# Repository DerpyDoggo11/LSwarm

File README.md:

# LSwarm Mk.1
Micro-drone swarm as a light display

## 3D Preview

## Wiring

## Schematic

### Download ./latestProduction to begin fabricating the PCB

## Introduction
The LSwarm Mk.1 is a cheap open-source microdrone platform for making drone swarms. Instead of GPS, it uses UWB frequencies to communicate with ground anchors (see [LS Anchor](https://github.com/DerpyDoggo11/LSwarm-Anchor)) for positioning. To fabricate these drones yourself, see the bill of materials below and follow the instructions. 

Also, its all open sourced under the GNU GPL license! (do what you will with the code and designs but make sure to keep it open-source! :D)

### Are drone swarms legal in the US?
TLDR: yes and no, mostly no but sometimes yes. 

In the US, flying more than one drone by yourself outside is technically not legal without a permit, but flying indoors (or under some netting outside) is perfectly allowed, so make sure you understand this before buying or assembling any components.

If you live outside of the US, your restrictions will be different so make sure to check with your local government. 

## Bill of Materials 

### (Minimum build for testing: 5 drones)

| Quantity | Components | Price | Link |
|--------- |----------|----------| -----|
| 20  | Brushed DC Motors | ~$9.68 | [here](https://www.aliexpress.us/item/3256810271706869.html?spm=a2g0o.productlist.main.48.18214690sK1aRt&algo_pvid=53df9bc5-14d9-4ef0-b69f-11a93d529ec5&algo_exp_id=53df9bc5-14d9-4ef0-b69f-11a93d529ec5-45&)
| 5  | 1s 450mAh BT2.0 Batteries | ~$11.21 | [here](https://www.aliexpress.us/item/3256810349502140.html?spm=a2g0o.productlist.main.9.7055TeWnTeWnyW&algo_pvid=e87d392e-a216-4ba3-8956-baf637a8cba3&algo_exp_id=e87d392e-a216-4ba3-8956-baf637a8cba3-8&pdp_ext_f=%7B%22order%22%3A%2248%22%2C%22eval%22%3A%221%22%2C%22fromPage%22%3A%22search%22%7D&pdp_npi=6%40dis%21USD%2113.57%216.78%21%21%2192.34%2146.17%21%402103110517771681621716757e4b37%2112000052738741335%21sea%21US%217493938711%21X%211%210%21n_tag%3A-29913%3Bd%3Ad260408f%3Bm03_new_user%3A-29895&curPageLogUid=6cUgOJiOwfNW&utparam-url=scene%3Asearch%7Cquery_from%3A%7Cx_object_id%3A1005010535816892%7C_p_origin_prod%3A)
| 1 | 1s BT2.0 Charger | ~18.18 | [here](https://www.aliexpress.us/item/3256811772590472.html?spm=a2g0o.productlist.main.3.315a3kxV3kxVU5&algo_pvid=a57de163-f3db-4a1d-966e-e88601147021&algo_exp_id=a57de163-f3db-4a1d-966e-e88601147021-2&pdp_ext_f=%7B%22order%22%3A%22-1%22%2C%22eval%22%3A%221%22%2C%22fromPage%22%3A%22search%22%7D&pdp_npi=6%40dis%21USD%2131.82%2119.09%21%21%21216.43%21129.86%21%402101f54117771690026201319e9264%2112000057143664294%21sea%21US%217493938711%21X%211%210%21n_tag%3A-29913%3Bd%3Ad260408f%3Bm03_new_user%3A-29895&curPageLogUid=pie8lE5eVKgd&utparam-url=scene%3Asearch%7Cquery_from%3A%7Cx_object_id%3A1005011958905224%7C_p_origin_prod%3A) 
|5 | 2.4G Wifi Antenna | ~$3.52 | [here](https://www.aliexpress.us/item/3256802833801038.html?spm=a2g0o.productlist.main.17.44bbCrBdCrBdFl&algo_pvid=20d56933-2b0c-45d5-8601-1bc6a9682401&algo_exp_id=20d56933-2b0c-45d5-8601-1bc6a9682401-16&pdp_ext_f=%7B%22order%22%3A%221074%22%2C%22eval%22%3A%221%22%2C%22fromPage%22%3A%22search%22%7D&pdp_npi=6%40dis%21USD%213.55%213.52%21%21%213.55%213.52%21%402101ef5e17781321493642302e40a6%2112000023272348781%21sea%21US%217493938711%21X%211%210%21n_tag%3A-29913%3Bd%3A21b1ce8d%3Bm03_new_user%3A-29895&curPageLogUid=rLnZuf4b98Bi&utparam-url=scene%3Asearch%7Cquery_from%3A%7Cx_object_id%3A1005003020115790%7C_p_origin_prod%3A)
| 5 | BMP581 (hand solder) | ~$20.34 | [here](https://www.lcsc.com/product-detail/C5362283.html?s_z=s_p_BMP581&spm=wm.ssy.bg.0.xh&lcsc_vid=EQdcXlMFQFgMVQUCQlALX1cFQVFeBlwHRgVYV1UAEwUxVlNRT1BfUFdfTlJcUDsOAxUeFF5JWBYZEEoKFBINSQcJGk4dAgUUFAk%3D)
| 5 | LSM6DSRTR (hand solder) | ~$17.33 | [here](https://www.lcsc.com/product-detail/C784817.html?s_z=s_q_LSM6DSR&spm=wm.ssy.bg.0.xh&lcsc_vid=EQdcXlMFQFgMVQUCQlALX1cFQVFeBlwHRgVYV1UAEwUxVlNRT1BfUFdTRFdfVDsOAxUeFF5JWBYZEEoKFBINSQcJGk4dAgUUFAk%3D)
| 5  | Mk.1 PCBs | ~$125 (with shipping, cost can vary widely however) | Download repo, extract fabrication files, and fabricate through JLCPCB (complete instructions for this may come soon)

Total cost: **$218.49**

Cost per drone: **$41.76**

----

### (Ideal build for full display: 20 drones)

| Quantity | Components | Price | Link |
|--------- |----------|----------| -----|
| 80  | Brushed DC Motors | ~$54.88  | [here](https://www.aliexpress.us/item/3256810271706869.html?spm=a2g0o.productlist.main.48.18214690sK1aRt&algo_pvid=53df9bc5-14d9-4ef0-b69f-11a93d529ec5&algo_exp_id=53df9bc5-14d9-4ef0-b69f-11a93d529ec5-45&)
| 20  | 1s 450mAh BT2.0 Batteries | ~$61.82  | [here](https://www.aliexpress.us/item/3256810349502140.html?spm=a2g0o.productlist.main.9.7055TeWnTeWnyW&algo_pvid=e87d392e-a216-4ba3-8956-baf637a8cba3&algo_exp_id=e87d392e-a216-4ba3-8956-baf637a8cba3-8&pdp_ext_f=%7B%22order%22%3A%2248%22%2C%22eval%22%3A%221%22%2C%22fromPage%22%3A%22search%22%7D&pdp_npi=6%40dis%21USD%2113.57%216.78%21%21%2192.34%2146.17%21%402103110517771681621716757e4b37%2112000052738741335%21sea%21US%217493938711%21X%211%210%21n_tag%3A-29913%3Bd%3Ad260408f%3Bm03_new_user%3A-29895&curPageLogUid=6cUgOJiOwfNW&utparam-url=scene%3Asearch%7Cquery_from%3A%7Cx_object_id%3A1005010535816892%7C_p_origin_prod%3A)
| 2 | 1s BT2.0 Charger | ~$36.36 | [here](https://www.aliexpress.us/item/3256811772590472.html?spm=a2g0o.productlist.main.3.315a3kxV3kxVU5&algo_pvid=a57de163-f3db-4a1d-966e-e88601147021&algo_exp_id=a57de163-f3db-4a1d-966e-e88601147021-2&pdp_ext_f=%7B%22order%22%3A%22-1%22%2C%22eval%22%3A%221%22%2C%22fromPage%22%3A%22search%22%7D&pdp_npi=6%40dis%21USD%2131.82%2119.09%21%21%21216.43%21129.86%21%402101f54117771690026201319e9264%2112000057143664294%21sea%21US%217493938711%21X%211%210%21n_tag%3A-29913%3Bd%3Ad260408f%3Bm03_new_user%3A-29895&curPageLogUid=pie8lE5eVKgd&utparam-url=scene%3Asearch%7Cquery_from%3A%7Cx_object_id%3A1005011958905224%7C_p_origin_prod%3A) 
| 20 | 2.4G Wifi Antenna | ~$14.08 | [here](https://www.aliexpress.us/item/3256802833801038.html?spm=a2g0o.productlist.main.17.44bbCrBdCrBdFl&algo_pvid=20d56933-2b0c-45d5-8601-1bc6a9682401&algo_exp_id=20d56933-2b0c-45d5-8601-1bc6a9682401-16&pdp_ext_f=%7B%22order%22%3A%221074%22%2C%22eval%22%3A%221%22%2C%22fromPage%22%3A%22search%22%7D&pdp_npi=6%40dis%21USD%213.55%213.52%21%21%213.55%213.52%21%402101ef5e17781321493642302e40a6%2112000023272348781%21sea%21US%217493938711%21X%211%210%21n_tag%3A-29913%3Bd%3A21b1ce8d%3Bm03_new_user%3A-29895&curPageLogUid=rLnZuf4b98Bi&utparam-url=scene%3Asearch%7Cquery_from%3A%7Cx_object_id%3A1005003020115790%7C_p_origin_prod%3A)
| 20 | BMP581 (hand solder) | ~$74.76 | [here](https://www.lcsc.com/product-detail/C5362283.html?s_z=s_p_BMP581&spm=wm.ssy.bg.0.xh&lcsc_vid=EQdcXlMFQFgMVQUCQlALX1cFQVFeBlwHRgVYV1UAEwUxVlNRT1BfUFdfTlJcUDsOAxUeFF5JWBYZEEoKFBINSQcJGk4dAgUUFAk%3D)
| 20 | LSM6DSRTR (hand solder) | ~$60.13 | [here](https://www.lcsc.com/product-detail/C784817.html?s_z=s_q_LSM6DSR&spm=wm.ssy.bg.0.xh&lcsc_vid=EQdcXlMFQFgMVQUCQlALX1cFQVFeBlwHRgVYV1UAEwUxVlNRT1BfUFdTRFdfVDsOAxUeFF5JWBYZEEoKFBINSQcJGk4dAgUUFAk%3D)
| 20  | Mk.1 PCBs | ~$200 (with shipping, cost can vary widely however) | Download repo, extract fabrication files, and fabricate through JLCPCB (complete instructions for this may come soon)

Total cost: **$562.95**

Cost per drone: **$25.40**

----

## Tools / Other parts:
- Raspberry PI Zero 2 W or equivalent (or just a computer/laptop)
- UWB Anchors ([LS Anchor](https://github.com/DerpyDoggo11/LSwarm-Anchor) or equivalent UWB module (must have wifi)) 
- Hot-air reflow station or SMD hot plate
- Solder paste for SMD components
- Tweezers for SMD components
- Soldering iron + solder
- Wire strippers/cutters
- Zipties, tape, or velcro straps
- Hot glue + hot glue gun

## Assembly
1. Apply solder paste onto the smd joints for the BMP581 and LSM6DSRTR.
2. Carefully align the components and place using tweezers
3. Use a hot-air gun (preferred over smd hot plate to not mess up any other components) on high heat to quickly heat up the solder paste (prolonged heat may damage components)
4. Fit motors into mounting holes (make sure they are aligned properly on all sides) use wire strippers to cut and solder on motor wires. Apply hot glue or equivalent to the motors to keep them in place.
5. Use wire strippers to cut and solder on battery connector wires to PCB.
6. Attach battery with velcro, zipties, or tape.
7. Plug in battery and flash software with the USB-C port.

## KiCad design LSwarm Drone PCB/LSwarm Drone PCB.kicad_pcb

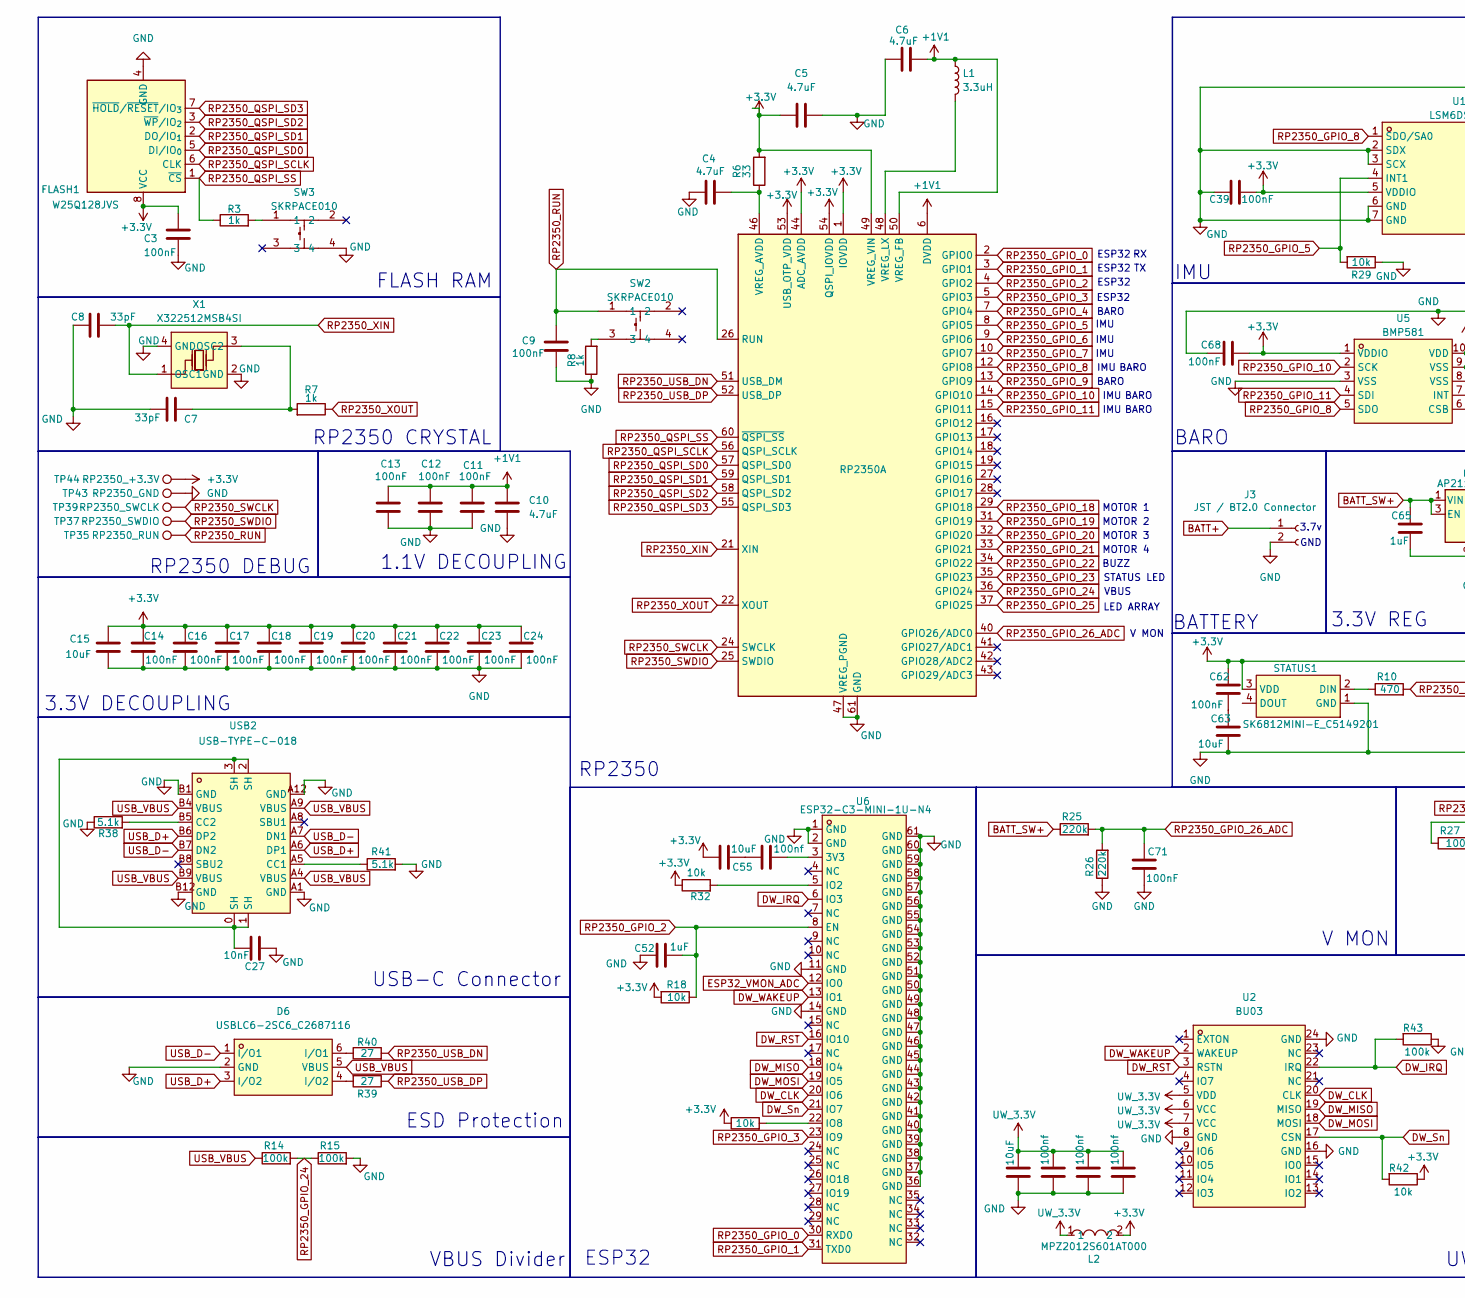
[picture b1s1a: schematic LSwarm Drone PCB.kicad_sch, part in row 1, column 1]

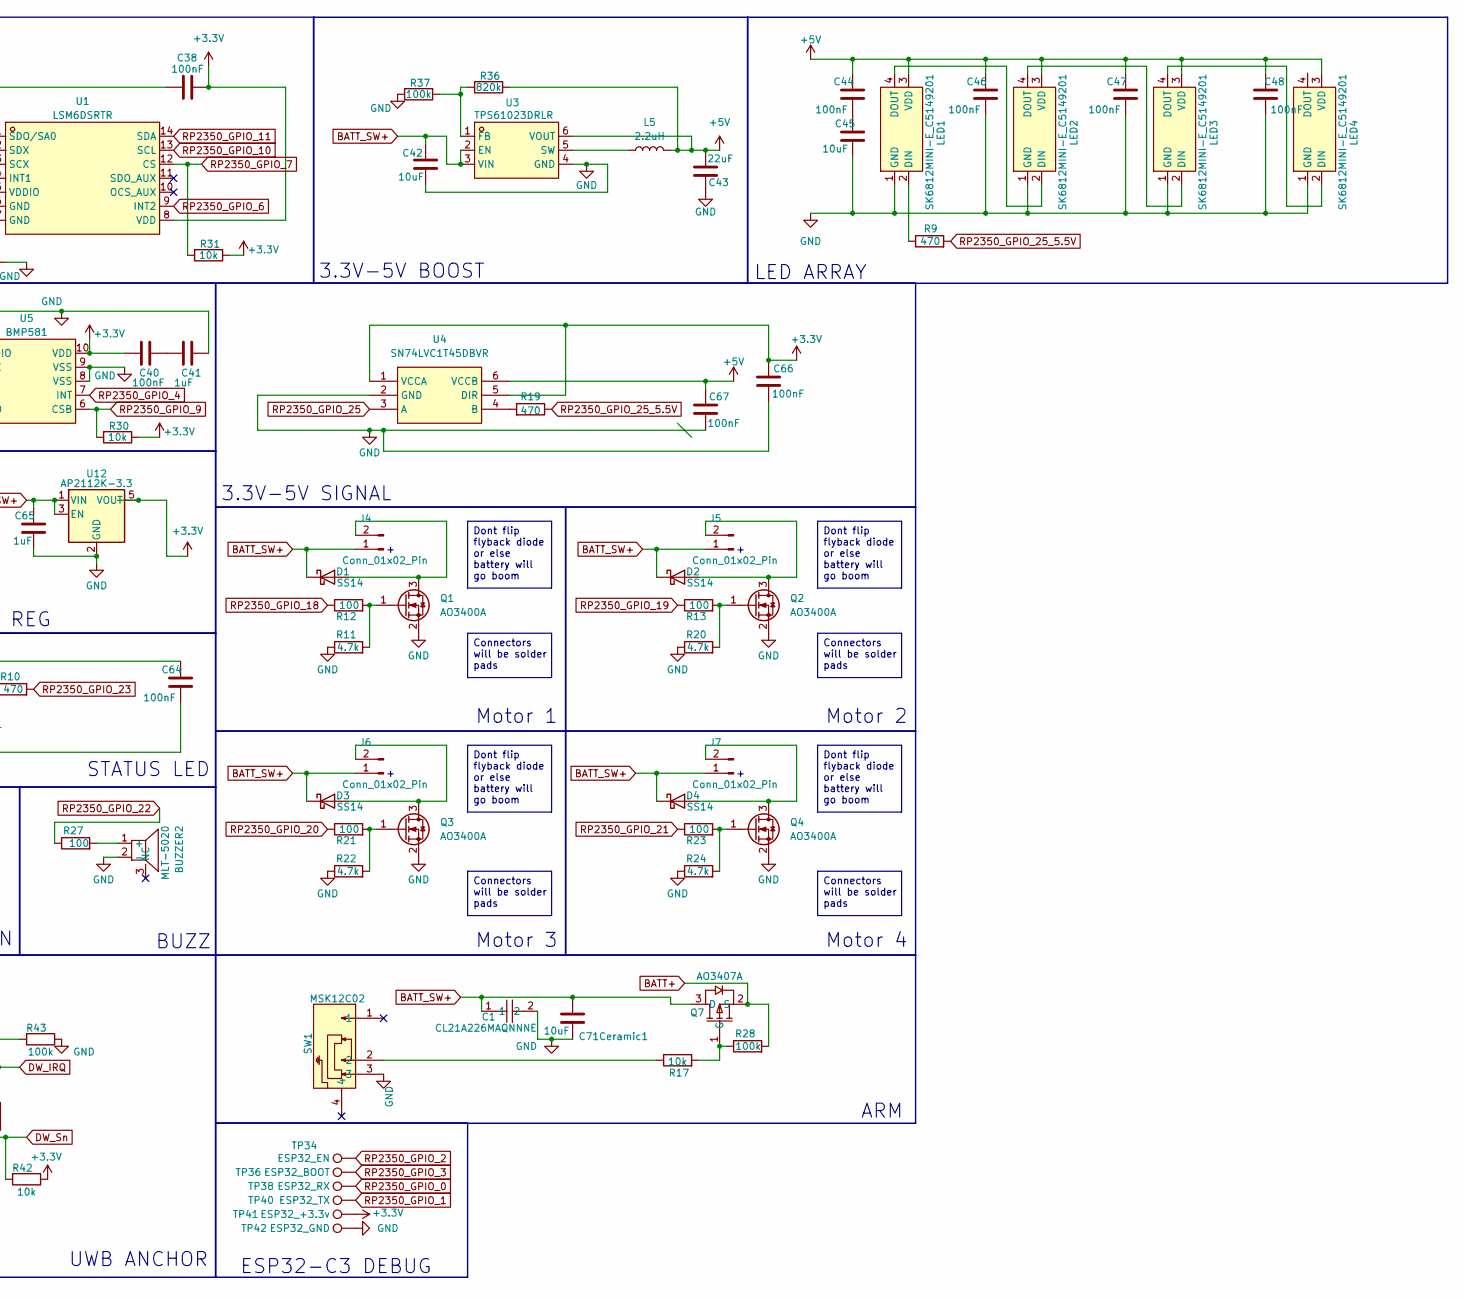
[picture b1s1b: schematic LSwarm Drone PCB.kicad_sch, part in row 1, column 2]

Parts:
BUZZER2: MLT-5020; BUZ-SMD_L5.0-W5.5-P4.60; MPN MLT-5020; LCSC Part C94598
C1: CL21A226MAQNNNE; C0805; MPN CL21A226MAQNNNE; LCSC Part C45783
C3, C9, C11, C12, C13, C14, C16, C17, C18, C19, C20, C21, C22, C23, C24, C38, C39, C40, C44, C46, C47, C48, C62, C64, C66, C67, C68, C71: 100nF; C_0603_1608Metric
C4, C5, C6, C10: 4.7uF; C_0603_1608Metric
C7, C8: 33pF; C_0603_1608Metric
C15, C42, C45, C63, C71Ceramic1: 10uF; C_0805_2012Metric
C27: 10nF; C_0603_1608Metric
C41, C52, C65: 1uF; C_0603_1608Metric
C43: 22uF; C_0805_2012Metric
C55, C69: 10uF; C_0603_1608Metric
C56, C58, C59, C61: 100nf; C_0603_1608Metric
D1, D2, D3, D4: SS14; D_SMA
D6: USBLC6-2SC6_C2687116; SOT-23-6_L2.9-W1.6-P0.95-LS2.8-BL; MPN USBLC6-2SC6; LCSC Part C2687116
FLASH1: W25Q128JVS; SOIC-8_5.3x5.3mm_P1.27mm
J3: JST / BT2.0 Connector; JST_PH_S2B-PH-K_1x02_P2.00mm_Horizontal
J4, J5, J6, J7: Conn_01x02_Pin; PinHeader_1x02_P2.54mm_Vertical
L1: 3.3uH; L_1210_3225Metric
L2: MPZ2012S601AT000; L0805; MPN MPZ2012S601AT000; LCSC Part C21519
L5: 2.2uH; L_1210_3225Metric
LED1, LED2, LED3, LED4: SK6812MINI-E_C5149201; LED-SMD_4P-L3.2-W2.8-LS5.9_SK6812MINI-E; MPN SK6812MINI-E; LCSC Part C5149201
Q1, Q2, Q3, Q4: AO3400A; SOT-23
Q7: AO3407A; SOT-23-3_L2.9-W1.6-P1.90-LS2.8-BR; MPN AO3407A; LCSC Part C15155
R3, R7, R8: 1k; R_0603_1608Metric
R6: 33; R_0603_1608Metric
R9, R10, R19: 470; R_0603_1608Metric
R11, R20, R22, R24: 4.7k; R_0603_1608Metric
R12, R13, R21, R23, R27: 100; R_0603_1608Metric
R14, R15, R28, R37, R43: 100k; R_0603_1608Metric
R17, R18, R29, R30, R31, R32, R33, R42: 10k; R_0603_1608Metric
R25, R26: 220k; R_0603_1608Metric
R36: 820k; R_0603_1608Metric
R38, R41: 5.1k; R_0603_1608Metric
R39, R40: 27; R_0603_1608Metric
RP2350: RP2350A; QFN-60-1EP_7x7mm_P0.4mm_EP3.4x3.4mm
STATUS1: SK6812MINI-E_C5149201; LED-SMD_4P-L3.2-W2.8-LS5.9_SK6812MINI-E; MPN SK6812MINI-E; LCSC Part C5149201
SW1: MSK12C02; SW-TH_MSK12C02; MPN MSK12C02; LCSC Part C431540
SW2, SW3: SKRPACE010; KEY-SMD_4P-L4.2-W3.2-P2.20-LS4.6; MPN SKRPACE010; LCSC Part C139797
TP34: ESP32_EN; TestPoint_Pad_1.0x1.0mm
TP35: RP2350_RUN; TestPoint_Pad_1.0x1.0mm
TP36: ESP32_BOOT; TestPoint_Pad_1.0x1.0mm
TP37: RP2350_SWDIO; TestPoint_Pad_1.0x1.0mm
TP38: ESP32_RX; TestPoint_Pad_1.0x1.0mm
TP39: RP2350_SWCLK; TestPoint_Pad_1.0x1.0mm
TP40: ESP32_TX; TestPoint_Pad_1.0x1.0mm
TP41: ESP32_+3.3v; TestPoint_Pad_1.0x1.0mm
TP42: ESP32_GND; TestPoint_Pad_1.0x1.0mm
TP43: RP2350_GND; TestPoint_Pad_1.0x1.0mm
TP44: RP2350_+3.3V; TestPoint_Pad_1.0x1.0mm
U1: LSM6DSRTR; LGA-14_L3.0-W2.5-P0.50-BR; MPN LSM6DSRTR; LCSC Part C784817
U2: BU03; WIRELM-SMD_BU03; MPN BU03; LCSC Part C42419011
U3: TPS61023DRLR; SOT-563_L1.6-W1.2-P0.50-LS1.6-BR; MPN TPS61023DRLR; LCSC Part C919459
U4: SN74LVC1T45DBVR; SOT-23-6_L2.9-W1.6-P0.95-LS2.8-BR; MPN SN74LVC1T45DBVR; LCSC Part C7843
U5: BMP581; LGA-10_L2.0-W2.0-P0.50-TL_BMP581; MPN BMP581; LCSC Part C5362283
U6: ESP32-C3-MINI-1U-N4; WIFIM-SMD_61P-L13.2-W12.5-P0.80; MPN ESP32-C3-MINI-1U-N4; LCSC Part C2911374
U12: AP2112K-3.3; SOT-23-5
USB2: USB-TYPE-C-018; USB-C_SMD-TYPE-C-31-M-12; MPN USB-TYPE-C-018; LCSC Part C2927038
X1: X322512MSB4SI; CRYSTAL-SMD_4P-L3.2-W2.5-BL; MPN X322512MSB4SI; LCSC Part C9002

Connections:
+1V1: C6.2, C10.1, C11.1, C12.1, C13.1, L1.1, RP2350.6 (DVDD), RP2350.23 (DVDD), RP2350.39 (DVDD), RP2350.50 (VREG_FB)
+3.3V: C3.1, C5.1, C14.1, C15.1, C16.1, C17.1, C18.1, C19.1, C20.1, C21.1, C22.1, C23.1, C24.1, C38.1, C39.1, C40.2, C55.2, C62.2, C64.2, C66.2, C68.1, FLASH1.8 (VCC), L2.2, R6.2, R18.2, R30.1, R31.1, R32.1, R33.1, R42.1, RP2350.1 (IOVDD), RP2350.11 (IOVDD), RP2350.20 (IOVDD), RP2350.30 (IOVDD), RP2350.38 (IOVDD), RP2350.44 (ADC_AVDD), RP2350.45 (IOVDD), RP2350.49 (VREG_VIN), RP2350.53 (USB_OTP_VDD), RP2350.54 (QSPI_IOVDD), STATUS1.3 (VDD), TP41.1 (1_1), TP44.1 (1_1), U1.5 (VDDIO), U1.8 (VDD), U4.1 (VCCA), U4.5 (DIR), U5.1 (VDDIO), U5.10 (VDD), U12.5 (VOUT)
+5V: C43.2, C44.2, C46.2, C47.2, C48.2, C67.2, L5.2, LED1.3 (VDD), LED2.3 (VDD), LED3.3 (VDD), LED4.3 (VDD), R36.1, U3.6 (VOUT), U4.6 (VCCB)
BATT+: J3.1, Q7.2 (S), R28.2
BATT_SW+: C1.1, C42.1, C65.2, C71Ceramic1.2, D1.1 (K), D2.1 (K), D3.1 (K), D4.1 (K), J4.1, J5.1, J6.1, J7.1, Q7.3 (D), R25.1, U3.2 (EN), U3.3 (VIN), U12.1 (VIN), U12.3 (EN)
DW_CLK: U2.20 (CLK), U6.20 (IO6)
DW_IRQ: R43.2, U2.22 (IRQ), U6.6 (IO3)
DW_MISO: U2.19 (MISO), U6.18 (IO4)
DW_MOSI: U2.18 (MOSI), U6.19 (IO5)
DW_RST: U2.3 (RSTN), U6.16 (IO10)
DW_Sn: R42.2, U2.17 (CSN), U6.21 (IO7)
DW_WAKEUP: U2.2 (WAKEUP), U6.13 (IO1)
ESP32_VMON_ADC: U6.12 (IO0)
GND: BUZZER2.2 (-), C1.2, C3.2, C4.1, C5.2, C6.1, C7.1, C8.2, C9.2, C10.2, C11.2, C12.2, C13.2, C14.2, C15.2, C16.2, C17.2, C18.2, C19.2, C20.2, C21.2, C22.2, C23.2, C24.2, C27.1, C38.2, C39.2, C41.1, C42.2, C43.1, C45.1, C46.1, C47.1, C48.1, C52.1, C58.2, C59.2, C61.2, C63.1, C64.1, C65.1, C66.1, C67.1, C68.2, C69.2, C71.1, C71Ceramic1.1, D6.2 (GND), FLASH1.4 (GND), J3.2, LED1.1 (GND), LED2.1 (GND), LED3.1 (GND), LED4.1 (GND), Q1.2 (S), Q2.2 (S), Q3.2 (S), Q4.2 (S), R8.1, R11.1, R15.2, R20.1, R22.1, R24.1, R26.1, R29.1, R37.2, R38.1, R41.2, R43.1, RP2350.47 (VREG_PGND), RP2350.61 (GND), STATUS1.1 (GND), SW1.3, SW3.4, TP42.1 (1_1), TP43.1 (1_1), U1.2 (SDX), U1.3 (SCX), U1.6 (GND), U1.7 (GND), U2.8 (GND), U2.16 (GND), U2.24 (GND), U3.4 (GND), U4.2 (GND), U5.3 (VSS), U5.8 (VSS), U5.9 (VSS), U6.1 (GND), U6.2 (GND), U6.11 (GND), U6.14 (GND), U6.36 (GND), U6.37 (GND), U6.38 (GND), U6.39 (GND), U6.40 (GND), U6.41 (GND), U6.42 (GND), U6.43 (GND), U6.44 (GND), U6.45 (GND), U6.46 (GND), U6.47 (GND), U6.48 (GND), U6.49 (GND), U6.50 (GND), U6.51 (GND), U6.52 (GND), U6.53 (GND), U6.54 (GND), U6.55 (GND), U6.56 (GND), U6.57 (GND), U6.58 (GND), U6.59 (GND), U6.60 (GND), U6.61 (GND), U12.2 (GND), USB2.A1 (GND), USB2.A12 (GND), USB2.B1 (GND), USB2.B12 (GND), X1.2 (GND), X1.4 (GND)
unnamed: BUZZER2.1 (+), R27.2
unnamed: C27.2, USB2.0 (SH), USB2.1 (SH), USB2.2 (SH), USB2.3 (SH)
unnamed: C40.1, C41.2
unnamed: C44.1, C45.2
unnamed: C55.1, C56.2
unnamed: C62.1, C63.2
unnamed: D1.2 (A), J4.2, Q1.3 (D)
unnamed: D2.2 (A), J5.2, Q2.3 (D)
unnamed: D3.2 (A), J6.2, Q3.3 (D)
unnamed: D4.2 (A), J7.2, Q4.3 (D)
unnamed: D6.6 (I/O1), R40.1
unnamed: D6.4 (I/O2), R39.2
unnamed: LED1.2 (DIN), R9.1
unnamed: LED1.4 (DOUT), LED2.2 (DIN)
unnamed: LED2.4 (DOUT), LED3.2 (DIN)
unnamed: LED3.4 (DOUT), LED4.2 (DIN)
unnamed: Q1.1 (G), R11.2, R12.2
unnamed: Q2.1 (G), R13.2, R20.2
unnamed: Q3.1 (G), R21.2, R22.2
unnamed: Q4.1 (G), R23.2, R24.2
unnamed: Q7.1 (G), R17.2, R28.1
unnamed: R3.2, SW3.1
unnamed: R8.2, SW2.3
unnamed: R17.1, SW1.2
unnamed: C4.2, R6.1, RP2350.46 (VREG_AVDD)
unnamed: L1.2, RP2350.48 (VREG_LX)
unnamed: R10.1, STATUS1.2 (DIN)
unnamed: R36.2, R37.1, U3.1 (FB)
unnamed: L5.1, U3.5 (SW)
unnamed: R19.2, U4.4 (B)
unnamed: C56.1, U6.3 (3V3)
unnamed: R32.2, U6.5 (IO2)
unnamed: R33.2, U6.22 (IO8)
unnamed: R41.1, USB2.A5 (CC1)
unnamed: R38.2, USB2.B5 (CC2)
unnamed: C7.2, R7.2, X1.3 (OSC2)
RP2350_GPIO_0: RP2350.2 (GPIO0), TP38.1 (1_1), U6.30 (RXD0)
RP2350_GPIO_1: RP2350.3 (GPIO1), TP40.1 (1_1), U6.31 (TXD0)
RP2350_GPIO_2: C52.2, R18.1, RP2350.4 (GPIO2), TP34.1 (1_1), U6.8 (EN)
RP2350_GPIO_3: RP2350.5 (GPIO3), TP36.1 (1_1), U6.23 (IO9)
RP2350_GPIO_4: RP2350.7 (GPIO4), U5.7 (INT)
RP2350_GPIO_5: R29.2, RP2350.8 (GPIO5), U1.4 (INT1)
RP2350_GPIO_6: RP2350.9 (GPIO6), U1.9 (INT2)
RP2350_GPIO_7: R31.2, RP2350.10 (GPIO7), U1.12 (CS)
RP2350_GPIO_8: RP2350.12 (GPIO8), U1.1 (SDO/SA0), U5.5 (SDO)
RP2350_GPIO_9: R30.2, RP2350.13 (GPIO9), U5.6 (CSB)
RP2350_GPIO_10: RP2350.14 (GPIO10), U1.13 (SCL), U5.2 (SCK)
RP2350_GPIO_11: RP2350.15 (GPIO11), U1.14 (SDA), U5.4 (SDI)
RP2350_GPIO_18: R12.1, RP2350.29 (GPIO18)
RP2350_GPIO_19: R13.1, RP2350.31 (GPIO19)
RP2350_GPIO_20: R21.1, RP2350.32 (GPIO20)
RP2350_GPIO_21: R23.1, RP2350.33 (GPIO21)
RP2350_GPIO_22: R27.1, RP2350.34 (GPIO22)
RP2350_GPIO_23: R10.2, RP2350.35 (GPIO23)
RP2350_GPIO_24: R14.2, R15.1, RP2350.36 (GPIO24)
RP2350_GPIO_25: RP2350.37 (GPIO25), U4.3 (A)
RP2350_GPIO_25_5.5V: R9.2, R19.1
RP2350_GPIO_26_ADC: C71.2, R25.2, R26.2, RP2350.40 (GPIO26/ADC0)
RP2350_QSPI_SCLK: FLASH1.6 (CLK), RP2350.56 (QSPI_SCLK)
RP2350_QSPI_SD0: FLASH1.5 (DI/IO_{0}), RP2350.57 (QSPI_SD0)
RP2350_QSPI_SD1: FLASH1.2 (DO/IO_{1}), RP2350.59 (QSPI_SD1)
RP2350_QSPI_SD2: FLASH1.3 (~WP/IO_{2}), RP2350.58 (QSPI_SD2)
RP2350_QSPI_SD3: FLASH1.7 (~HOLD/~RESET/IO_{3}), RP2350.55 (QSPI_SD3)
RP2350_QSPI_SS: FLASH1.1 (~CS), R3.1, RP2350.60 (~QSPI_SS)
RP2350_RUN: C9.1, RP2350.26 (RUN), SW2.1, TP35.1 (1_1)
RP2350_SWCLK: RP2350.24 (SWCLK), TP39.1 (1_1)
RP2350_SWDIO: RP2350.25 (SWDIO), TP37.1 (1_1)
RP2350_USB_DN: R40.2, RP2350.51 (USB_DM)
RP2350_USB_DP: R39.1, RP2350.52 (USB_DP)
RP2350_XIN: C8.1, RP2350.21 (XIN), X1.1 (OSC1)
RP2350_XOUT: R7.1, RP2350.22 (XOUT)
USB_D+: D6.3 (I/O2), USB2.A6 (DP1), USB2.B6 (DP2)
USB_D-: D6.1 (I/O1), USB2.A7 (DN1), USB2.B7 (DN2)
USB_VBUS: D6.5 (VBUS), R14.1, USB2.A4 (VBUS), USB2.A9 (VBUS), USB2.B4 (VBUS), USB2.B9 (VBUS)
UW_3.3V: C58.1, C59.1, C61.1, C69.1, L2.1, U2.5 (VDD), U2.6 (VCC), U2.7 (VCC)

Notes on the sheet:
GND
3.3V DECOUPLING
RP2350 DEBUG
IMU
LED ARRAY
BARO
VBUS
ESP32-C3 DEBUG
UWB ANCHOR
VBUS Divider
Motor 4
ESP32
3.3V-5V SIGNAL
Motor 1
USB-C Connector
BUZZ
1.1V DECOUPLING
STATUS LED
BATTERY
RP2350 CRYSTAL
MOTOR 1
ESD Protection
3.3V-5V BOOST
Motor 2
ARM
MOTOR 2
MOTOR 3
MOTOR 4
RP2350
FLASH RAM
V MON
3.7v
Motor 3
V MON
3.3V REG
Connectors will be solder pads
Dont flip flyback diode or else battery will go boom

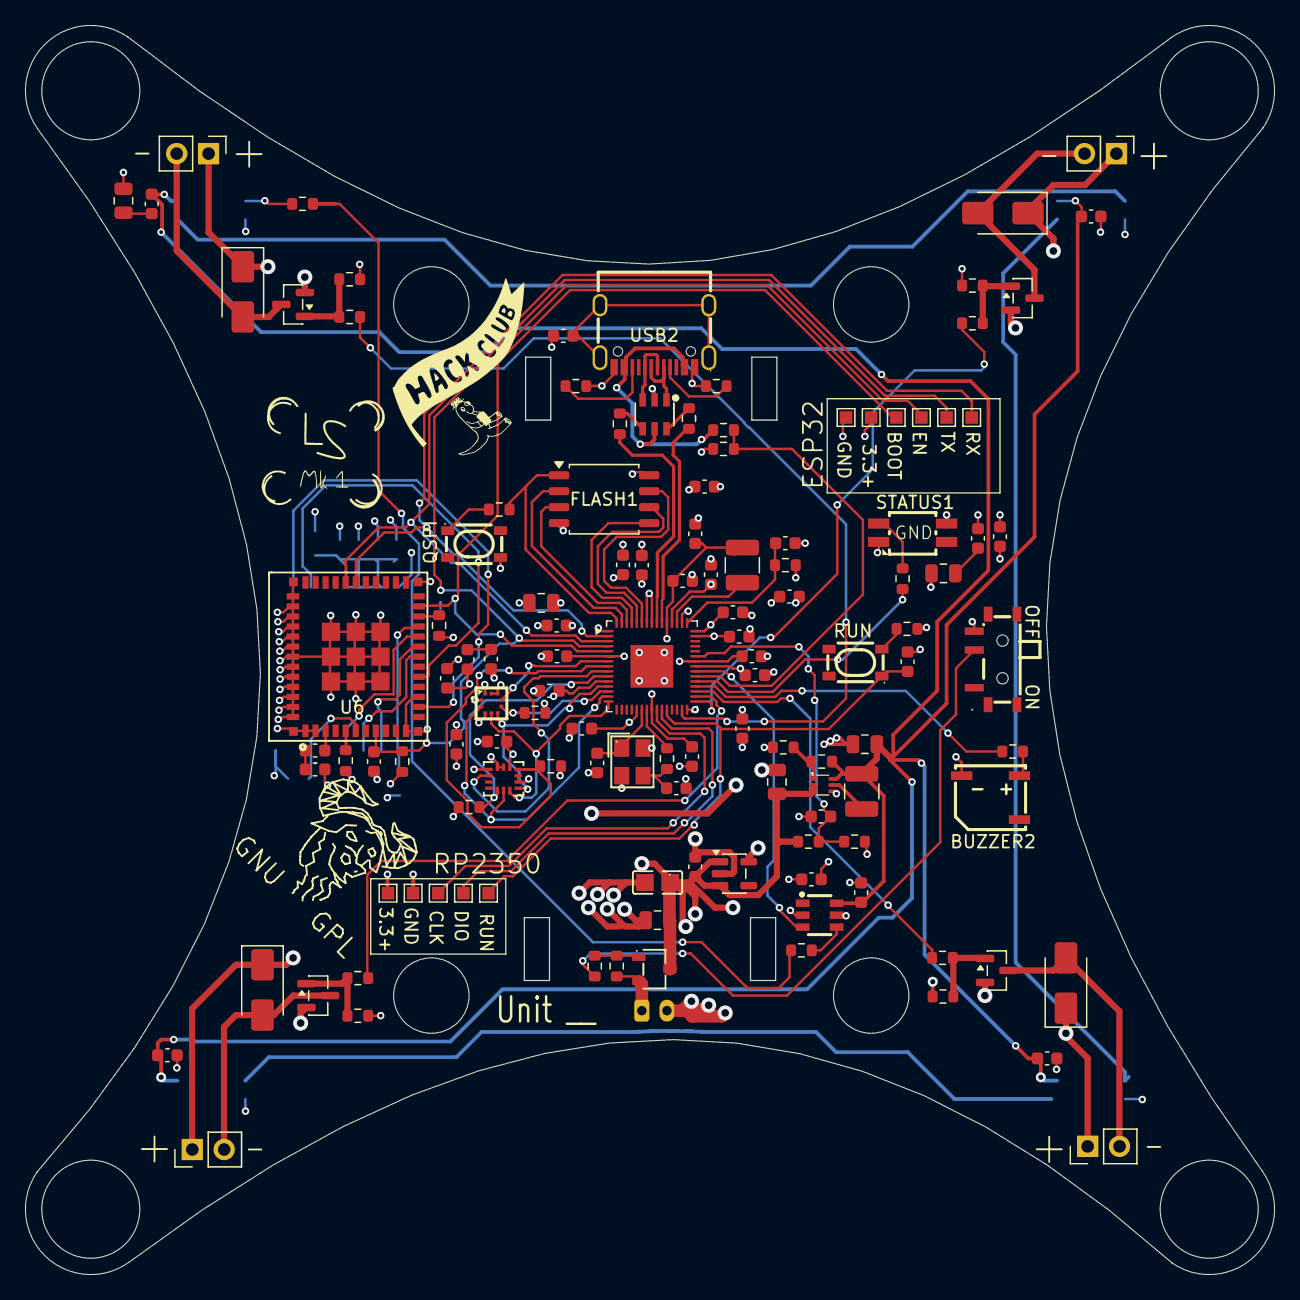
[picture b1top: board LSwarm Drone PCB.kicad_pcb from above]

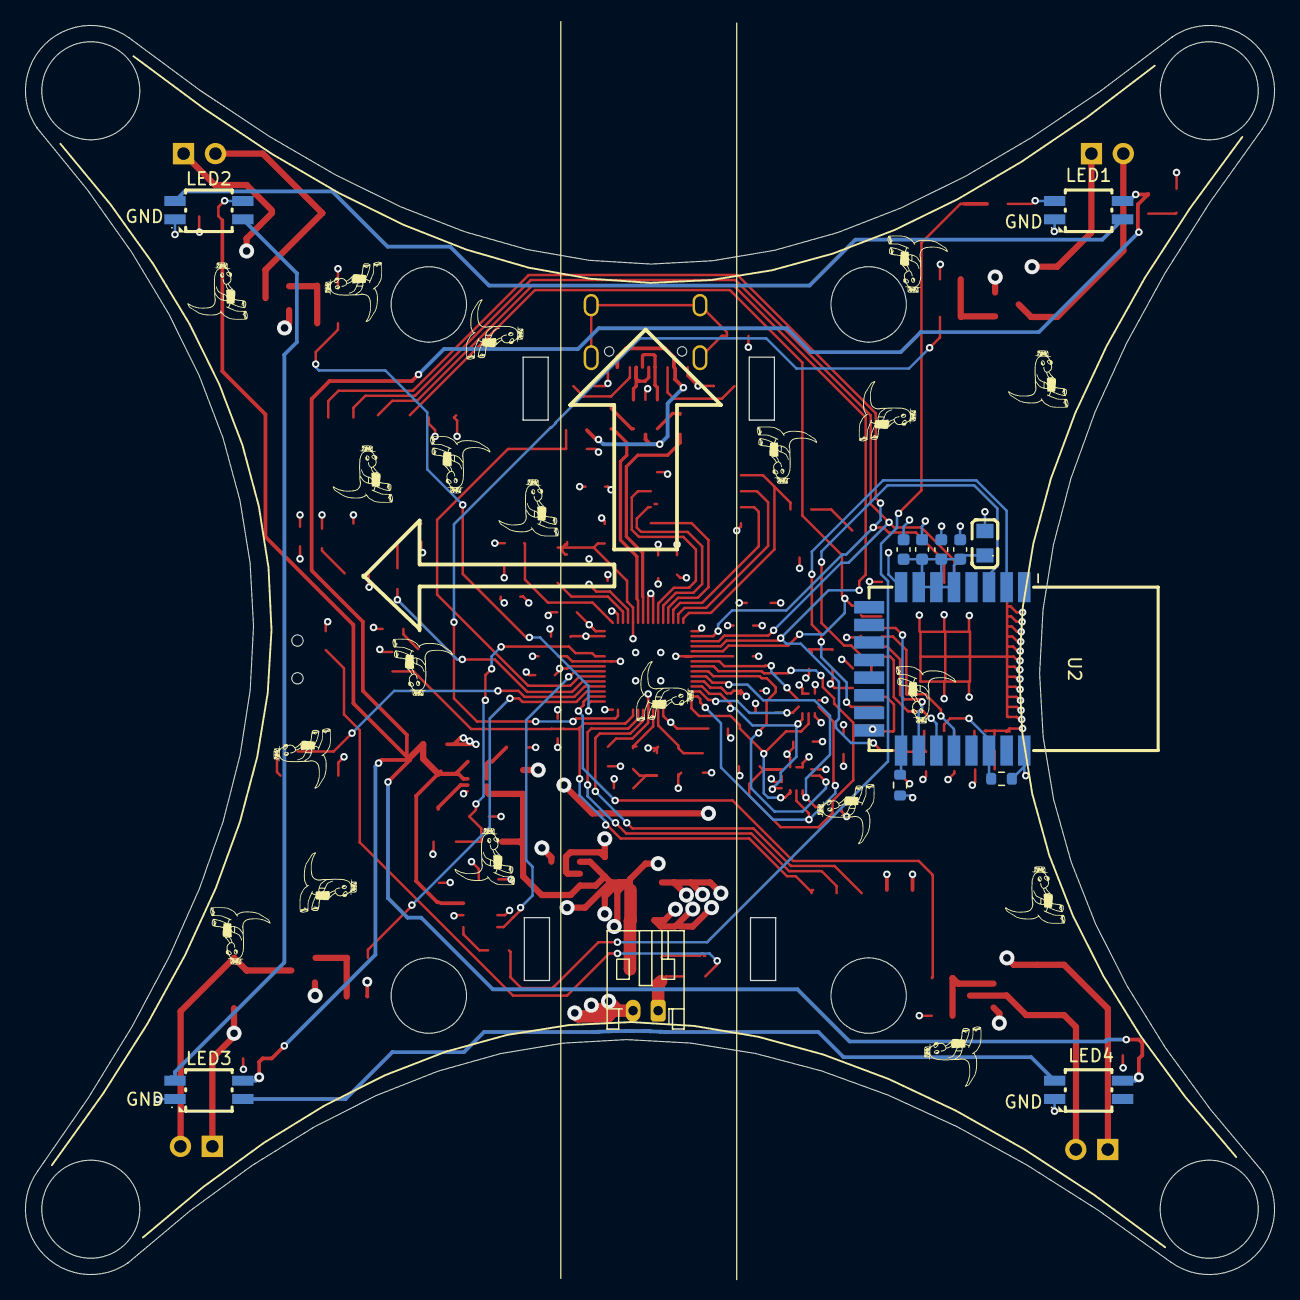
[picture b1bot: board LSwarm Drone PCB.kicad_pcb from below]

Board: 4 copper layers, 99.4 x 99.4 mm, 160 parts (33 on the bottom side), 88 nets.

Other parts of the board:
GNU: Symbol_GNU-Logo_SilkscreenTop
dino: LOGO; dino
dino#2, dino#3, dino#4, dino#5, dino#6, dino#7, dino#8, dino#9, dino#10, dino#11, dino#12, dino#13, dino#14, dino#15, dino#16, dino#17, dino#18, dino#19, dino#20, dino#21: LOGO; dino
hackclub: LOGO; hackclub
logo: LOGO; mk1Logo

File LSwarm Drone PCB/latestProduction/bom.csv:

Designator,Footprint,Quantity,Value,LCSC Part #
BUZZER2,BUZ-SMD_L5.0-W5.5-P4.60,1,MLT-5020,C94598
"C10, C4, C5, C6",0603,4,4.7uF,
"C11, C12, C13, C14, C16, C17, C18, C19, C20, C21, C22, C23, C24, C3, C38, C39, C40, C44, C46, C47, C48, C49, C50, C51, C53, C56, C57, C58, C62, C64, C66, C67, C68, C71, C9",0603,35,100nF,
"C15, C42, C45, C63, C71CERAMIC1",0805,5,10uF,
"C26, C54",0603,2,10nF,
"C41, C59, C65",0603,3,1uF,
C43,0805,1,22uF,
"C52, C55",0603,2,12pF,
"C60, C61",0603,2,3.3pF,
"C7, C8",0603,2,15pF,
C72,CP_EIA-3528-21_Kemet-B,1,220uF,
"D1, D2, D3, D4",D_SMA,4,SS14,
ESP32,QFN-32-1EP_5x5mm_P0.5mm_EP3.7x3.7mm,1,ESP32-C3,
FLASH1,SOIC-8_5.3x5.3mm_P1.27mm,1,W25Q128JVS,
,,,,
,,,,
,,,,
JP1,RF-SMD_FRF05002-JSS103M,1,U.FL-R-SMT-1,C88374
L1,1210,1,3.3uH,
L5,1210,1,2.2uH,
L6,0805,1,24nH,
L7,0402,1,2nH,
L8,0402,1,2.2nH,
"LED1, LED2, LED3, LED4, STATUS1",LED-SMD_4P-L3.2-W2.8-LS5.9_SK6812MINI-E,5,SK6812MINI-E_C5149201,C5149201
"Q1, Q2, Q3, Q4",SOT-23,4,AO3400A,
Q7,SOT-23-3_L2.9-W1.6-P1.90-LS2.8-BR,1,AO3407A,C15155
"R10, R19, R9",0603,3,470,
"R11, R20, R22, R24",0603,4,4.7k,
"R12, R13, R21, R23, R27",0603,5,100,
"R14, R15, R16, R29, R30, R31",0603,6,10k,
R17,0603,1,806k,
R18,0603,1,110k,
"R25, R26",0603,2,220k,
R28,0603,1,100k,
"R3, R7, R8",0603,3,1k,
"R32, R33",0603,2,5.1k,
"R34, R35",0603,2,27,
R6,0603,1,33,
RP2350,QFN-60-1EP_7x7mm_P0.4mm_EP3.4x3.4mm,1,RP2350A,
SW1,SW-TH_MSK12C02,1,MSK12C02,C431540
"SW2, SW3, SW4, SW5",KEY-SMD_4P-L4.2-W3.2-P2.20-LS4.6,4,SKRPACE010,C139797
U1,LGA-14_L3.0-W2.5-P0.50-BR,1,LSM6DSRTR,C784817
U12,SOT-23-5,1,AP2112K-3.3,
U2,CRYSTAL-SMD_4P-L3.2-W2.5-BL,1,ABM8-272-T3_C20625731,C20625731
U3,SOT-563_L1.6-W1.2-P0.50-LS1.6-BR,1,TPS61023DRLR,C919459
U4,SOT-23-6_L2.9-W1.6-P0.95-LS2.8-BR,1,SN74LVC1T45DBVR,C7843
U5,LGA-10_L2.0-W2.0-P0.50-TL_BMP581,1,BMP581,C5362283
USB1,USB-C_SMD-TYPE-C-31-M-12,1,USB-TYPE-C-018,C2927038
Y3,Crystal_SMD_3225-4Pin_3.2x2.5mm,1,40MHz,

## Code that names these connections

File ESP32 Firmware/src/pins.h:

#pragma once
#include <cstdint>

// ---------------------------------------------------------------------------
// External ESP32-S3 Super Mini pin map (drone).
//
// The on-board ESP32-C3-MINI (U8) is bypassed. An external ESP32-S3 Super Mini
// is wired to the 6-pin "ESP32" header (GND 3V3 BOOT EN TX RX) for the RP2350
// link, and (optionally) to a DW3000 UWB add-on module for anchor ranging.
//
// Pick only "safe" S3 GPIOs. Avoid 0/3/45/46 (strapping), 19/20 (USB), 43/44
// (USB-serial-jtag TX/RX) and 48 (on-board RGB LED).
// ---------------------------------------------------------------------------

// UART link to the RP2350 (Serial1). Cross-wired at the header:
//   header TX (RP2350 GPIO0, RP2350 out) -> S3 RX below
//   header RX (RP2350 GPIO1, RP2350 in)  <- S3 TX below
static constexpr int PIN_LINK_RX = 4;
static constexpr int PIN_LINK_TX = 5;
static constexpr uint32_t LINK_BAUD = 115200;

// On-board DW3000 UWB tag (SPI). The tag is on the drone PCB; its DW nets route
// to the dead ESP32-C3 pads. Tap them there and run to these S3 GPIOs. The C3
// pin each DW net lands on (find the pad):
//   WAKEUP=C3 IO1  IRQ=C3 IO3  MISO=C3 IO4  MOSI=C3 IO5
//   CLK=C3 IO6     CS=C3 IO7   RST=C3 IO10
static constexpr int PIN_DW_MOSI   = 11;
static constexpr int PIN_DW_SCK    = 12;
static constexpr int PIN_DW_MISO   = 13;
static constexpr int PIN_DW_CS     = 10;
static constexpr int PIN_DW_IRQ    = 9;
static constexpr int PIN_DW_RST    = 8;
static constexpr int PIN_DW_WAKEUP = 7;

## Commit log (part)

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2026-04-17 init
2026-04-17 sync
2026-04-25 finished the schematic!!!!
2026-04-25 imported components correctly into the pcb wiring design
2026-04-28 finished pcb layout
2026-04-28 finished main wiring
2026-04-29 added graphics + other stuff
2026-05-06 sync (todo: add images to readme)
2026-05-06 added images to readme
2026-06-10 finished new pcb wiring
2026-06-20 added vbus connection to rp2350
